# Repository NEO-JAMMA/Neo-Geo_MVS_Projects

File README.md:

THIS PROJECT IS PROVIDED "AS IS", WITHOUT WARRANTY OF ANY KIND, EXPRESS OR IMPLIED, INCLUDING BUT NOT LIMITED TO THE WARRANTIES OF MERCHANTABILITY, FITNESS FOR A PARTICULAR PURPOSE AND NONINFRINGEMENT. IN NO EVENT SHALL I BE LIABLE FOR ANY CLAIM, DAMAGES OR OTHER LIABILITY, WHETHER IN AN ACTION OF CONTRACT, TORT OR OTHERWISE, ARISING FROM, OUT OF OR IN CONNECTION WITH THIS PROJECT.

<b>Supergun for all MVS:</b><br>
https://github.com/NEO-JAMMA/Neo-Geo_MVS_Projects/tree/main/Supergun

<b>SNES to Neo-Geo Controller Adapter</b><br>
https://github.com/NEO-JAMMA/Neo-Geo_MVS_Projects/tree/main/ControllerAdapter

<b>RGB Csync to YPbPr NTSC Converter</b><br>
https://github.com/NEO-JAMMA/Neo-Geo_MVS_Projects/tree/main/RGBsToYPrBr

<b>Battery holder for MV1-C and MV1-B:</b><br>
https://github.com/NEO-JAMMA/Neo-Geo_MVS_Projects/blob/main/Battery

<b>Stereo mod is for MV1-B, MV1-A, and MV1FZ:</b><br>
https://github.com/NEO-JAMMA/Neo-Geo_MVS_Projects/blob/main/StereoMod

<b>ESP8266 Adapter for GBS8200</b><br>
https://github.com/NEO-JAMMA/Neo-Geo_MVS_Projects/blob/main/Esp8266ToGbs8200

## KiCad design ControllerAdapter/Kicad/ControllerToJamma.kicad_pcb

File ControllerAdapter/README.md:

THIS PROJECT IS PROVIDED "AS IS", WITHOUT WARRANTY OF ANY KIND, EXPRESS OR IMPLIED, INCLUDING BUT NOT LIMITED TO THE WARRANTIES OF MERCHANTABILITY, FITNESS FOR A PARTICULAR PURPOSE AND NONINFRINGEMENT. IN NO EVENT SHALL I BE LIABLE FOR ANY CLAIM, DAMAGES OR OTHER LIABILITY, WHETHER IN AN ACTION OF CONTRACT, TORT OR OTHERWISE, ARISING FROM, OUT OF OR IN CONNECTION WITH THIS PROJECT.

<b>SNES to Neo-Geo Controller Adapter</b>

<b>This converter is design to works with MVS supergun</b>
https://github.com/NEO-JAMMA/Neo-Geo_MVS_Projects/tree/main/Supergun/README.md

<b>Pictures of the all the Parts:</b><br>
https://github.com/NEO-JAMMA/Neo-Geo_MVS_Projects/tree/main/ControllerAdapter/Parts

<b>Parts description:</b>
- 1 * Arduino Nano (Cheap clone will works fine)
- 2 * Header 15 pins 2.54mm
- 1 * Micro Slide 90 Degree Switch 6 Pins DPDT PCB Mount
- 1 * Super Nintendo/Super Famicom controller port 90 Degree 7 Pin Female (if the controller port is reversed it is possible to reverse the pins by polling them and turning them to a 180 degree angle)
- 1 * DR15 15 Pins female right angle (D-SUB 15)
- 2 * Flat M3 Screws to replace the long hexagonal screw of DR15 15 Pins female port (to secure the front metal connector)

<b>Optional parts:</b>
- 4 * M2 Screws 25mm to 28mm long (For 3D printed case)

<b>Gerber files:</b><br>
https://github.com/NEO-JAMMA/Neo-Geo_MVS_Projects/tree/main/ControllerAdapter/Gerber

<b>Arduino code:</b><br>
https://github.com/NEO-JAMMA/Neo-Geo_MVS_Projects/tree/main/ControllerAdapter/ArduinoCode

<b>3D Printed case:</b><br>
https://github.com/NEO-JAMMA/Neo-Geo_MVS_Projects/tree/main/ControllerAdapter/3D_Case

<b>Kicad source:</b><br>
https://github.com/NEO-JAMMA/Neo-Geo_MVS_Projects/tree/main/ControllerAdapter/Kicad

<b>Controller Modes:</b><br>
The mode switch on the side of the PCB toggle the button mappings

<b>Other:</b>
- The controller adapter will have work with a Neo-Geo AES unfortunately the DB15 port is too short for Neo-Geo AES controller port.
- To program the Arduino Nano please refer to https://docs.arduino.cc/tutorials/nano/nano-getting-started/.
- The controller adapter works with Super Nintendo or Super Famicom controller (Cheap clones are fine).

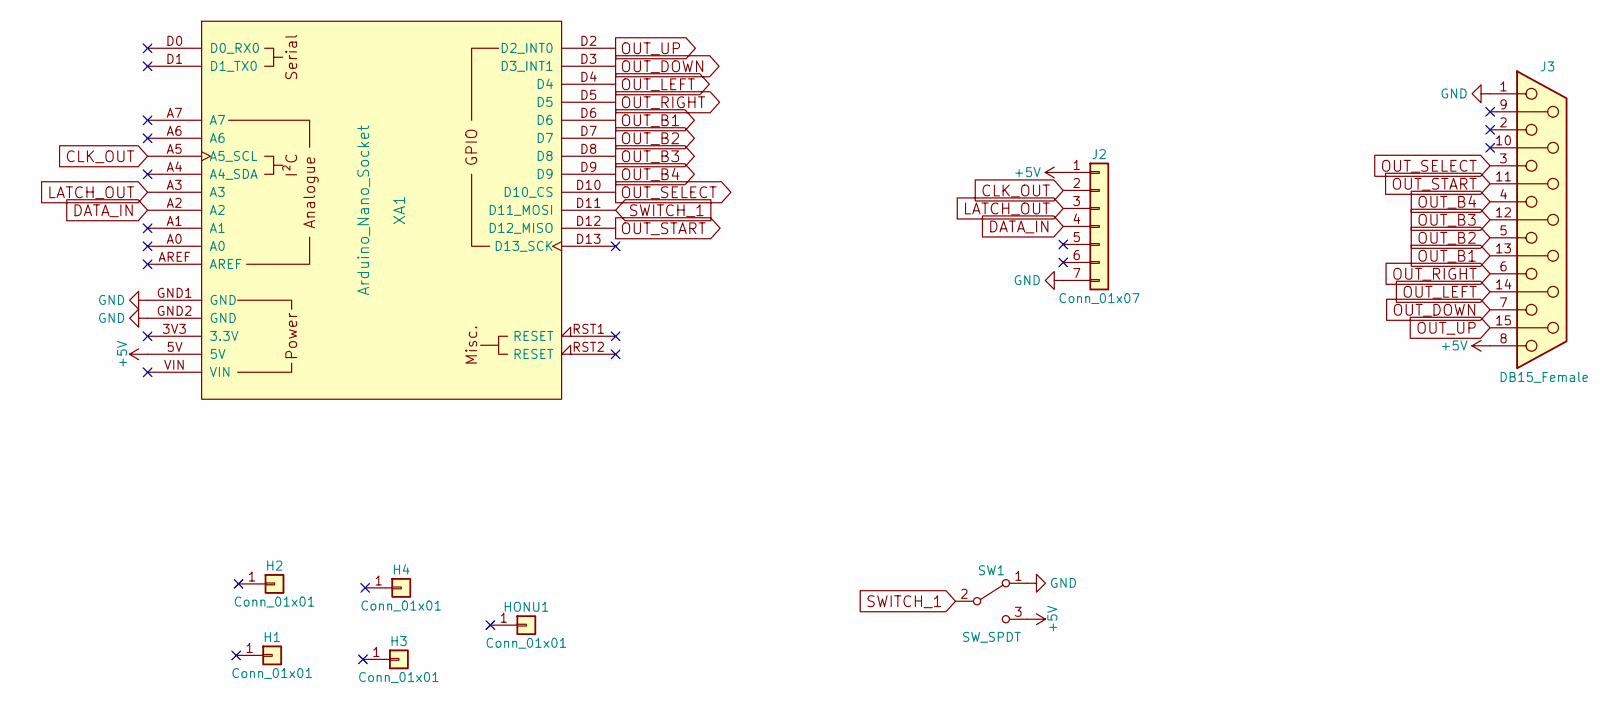
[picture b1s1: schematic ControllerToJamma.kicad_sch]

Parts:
H1, H2, H3, H4: Conn_01x01; MountingHole_2.5mm
HONU1: Conn_01x01; logo
J2: Conn_01x07; SNES_controller_port
J3: DB15_Female; DSUB-15_Female_Horizontal_Pitch2.77x2.84mm_EdgePinOffset4.9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
SW1: SW_SPDT; JS202011CQN
XA1: Arduino_Nano_Socket

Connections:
+5V: J2.1, J3.8, SW1.3 (C), XA1.5V
CLK_OUT: J2.2, XA1.A5 (A5_SCL)
DATA_IN: J2.4, XA1.A2
LATCH_OUT: J2.3, XA1.A3
OUT_B1: J3.13, XA1.D6
OUT_B2: J3.5, XA1.D7
OUT_B3: J3.12, XA1.D8
OUT_B4: J3.4, XA1.D9
OUT_DOWN: J3.7, XA1.D3 (D3_INT1)
OUT_LEFT: J3.14, XA1.D4
OUT_RIGHT: J3.6, XA1.D5
OUT_SELECT: J3.3, XA1.D10 (D10_CS)
OUT_START: J3.11 (P111), XA1.D12 (D12_MISO)
OUT_UP: J3.15, XA1.D2 (D2_INT0)
SWITCH_1: SW1.2 (B), XA1.D11 (D11_MOSI)
~: J2.7, J3.1, SW1.1 (A), XA1.GND1 (GND), XA1.GND2 (GND)

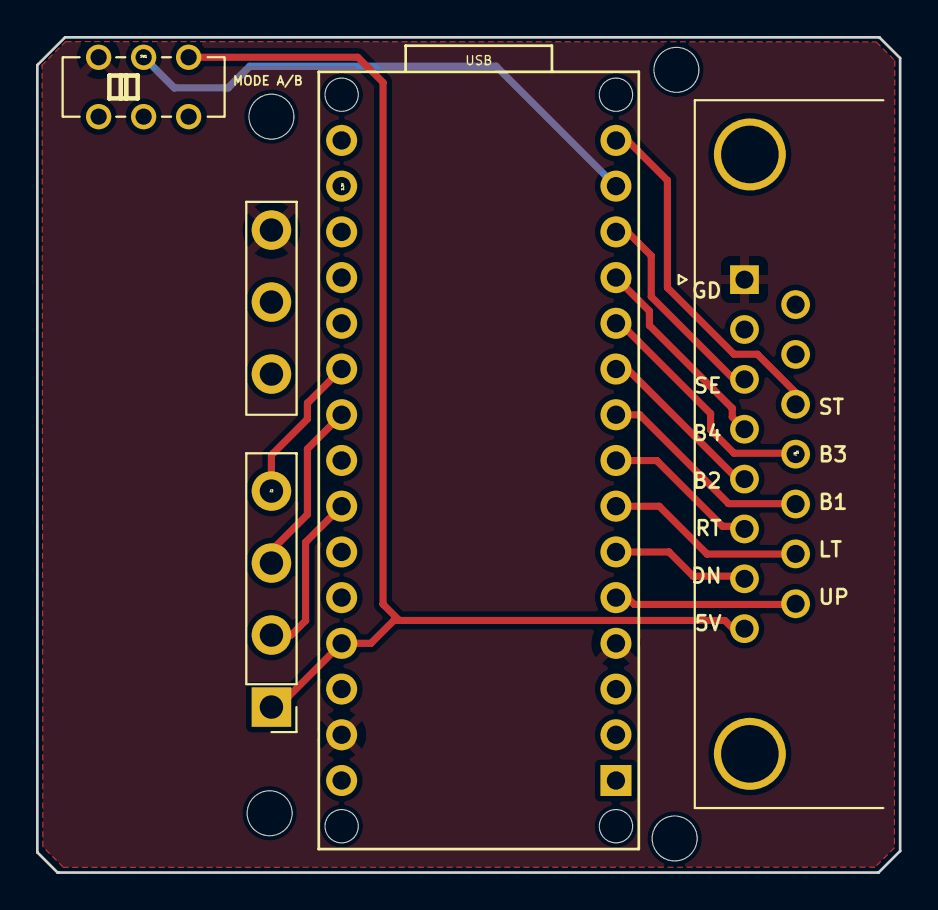
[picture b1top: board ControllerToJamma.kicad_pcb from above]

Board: 2 copper layers, 47.9 x 46.4 mm, 9 parts (1 on the bottom side), 16 nets.

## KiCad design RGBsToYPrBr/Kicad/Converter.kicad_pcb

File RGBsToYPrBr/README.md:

THIS PROJECT IS PROVIDED "AS IS", WITHOUT WARRANTY OF ANY KIND, EXPRESS OR IMPLIED, INCLUDING BUT NOT LIMITED TO THE WARRANTIES OF MERCHANTABILITY, FITNESS FOR A PARTICULAR PURPOSE AND NONINFRINGEMENT. IN NO EVENT SHALL I BE LIABLE FOR ANY CLAIM, DAMAGES OR OTHER LIABILITY, WHETHER IN AN ACTION OF CONTRACT, TORT OR OTHERWISE, ARISING FROM, OUT OF OR IN CONNECTION WITH THIS PROJECT.

<b>RGB Csync to YPbPr NTSC Converter</b>

<b>This Converter is design for this Supergun:</b><br>
https://github.com/NEO-JAMMA/Neo-Geo_MVS_Projects/tree/main/Supergun

<b>Pictures of the all the Parts:</b><br>

<b>Parts description:</b>
- 3 * 16V 220UF 6x7mm Electrolytic Capacitors
- 3 * 50V 1UF 4x7mm Electrolytic Capacitors
- 1 * 50V 10UF 4x7mm Electrolytic Capacitors
- 1 * 0.1UF Capacitors (104)
- 1 * 0.047UF Capacitors (473)
- 3 * 2sc945 transistors
- 1 * NTSC signal encoder BA7230LS
- 3 * PCB Mount RCA Female Connector
- 1 * 3F07 Audio Jack Connector PCB 5 Pins
- 1 * Header 8 Pins Male Socket Double Row 2.54mm (AV connection to the Supergun)
- 1 * 8 pins Dupont Cable Female Connector Wire 2.54mm Pitch 30cm (AV connection to the Supergun)
- 9 * Resistors
    - 6 * 75 Ohm
    - 2 * 20 Ohm
    - 1 * 62 Ohm

<b>Optional parts for powering the Supergun from the converter:</b>
- 3 * 18 gauge wires (12 Volt, 5 Volt, and ground connection to the Supergun)
- 1 * Molex 4 pins (PC connector)(12 Volt and 5 Volt connection to the Supergun)
- 1 * Power Jack Socket 2.1mm x 5.5mm Barrel-Type PCB Mount (5 Volt connection to the Supergun)

<b>Gerber files:</b><br>
https://github.com/NEO-JAMMA/Neo-Geo_MVS_Projects/tree/main/RGBsToYPrBr/Gerber

<b>Kicad source:</b><br>
https://github.com/NEO-JAMMA/Neo-Geo_MVS_Projects/tree/main/RGBsToYPrBr/Kicad

<b>Other:</b>
- The converter can also power the Supergun (see optional parts section)
- Acknowledgements to Ace, Zebidee and all variations available on the web which helped me for the design.
- Works only with NTSC TV not PAL/SECAM
- Only dislpay in 240p. For modern HDMI TV you need an upscaler like:
    - OSSC (https://www.retrorgb.com/ossc.html)
    - GBS8200 (https://github.com/ramapcsx2/gbs-control)

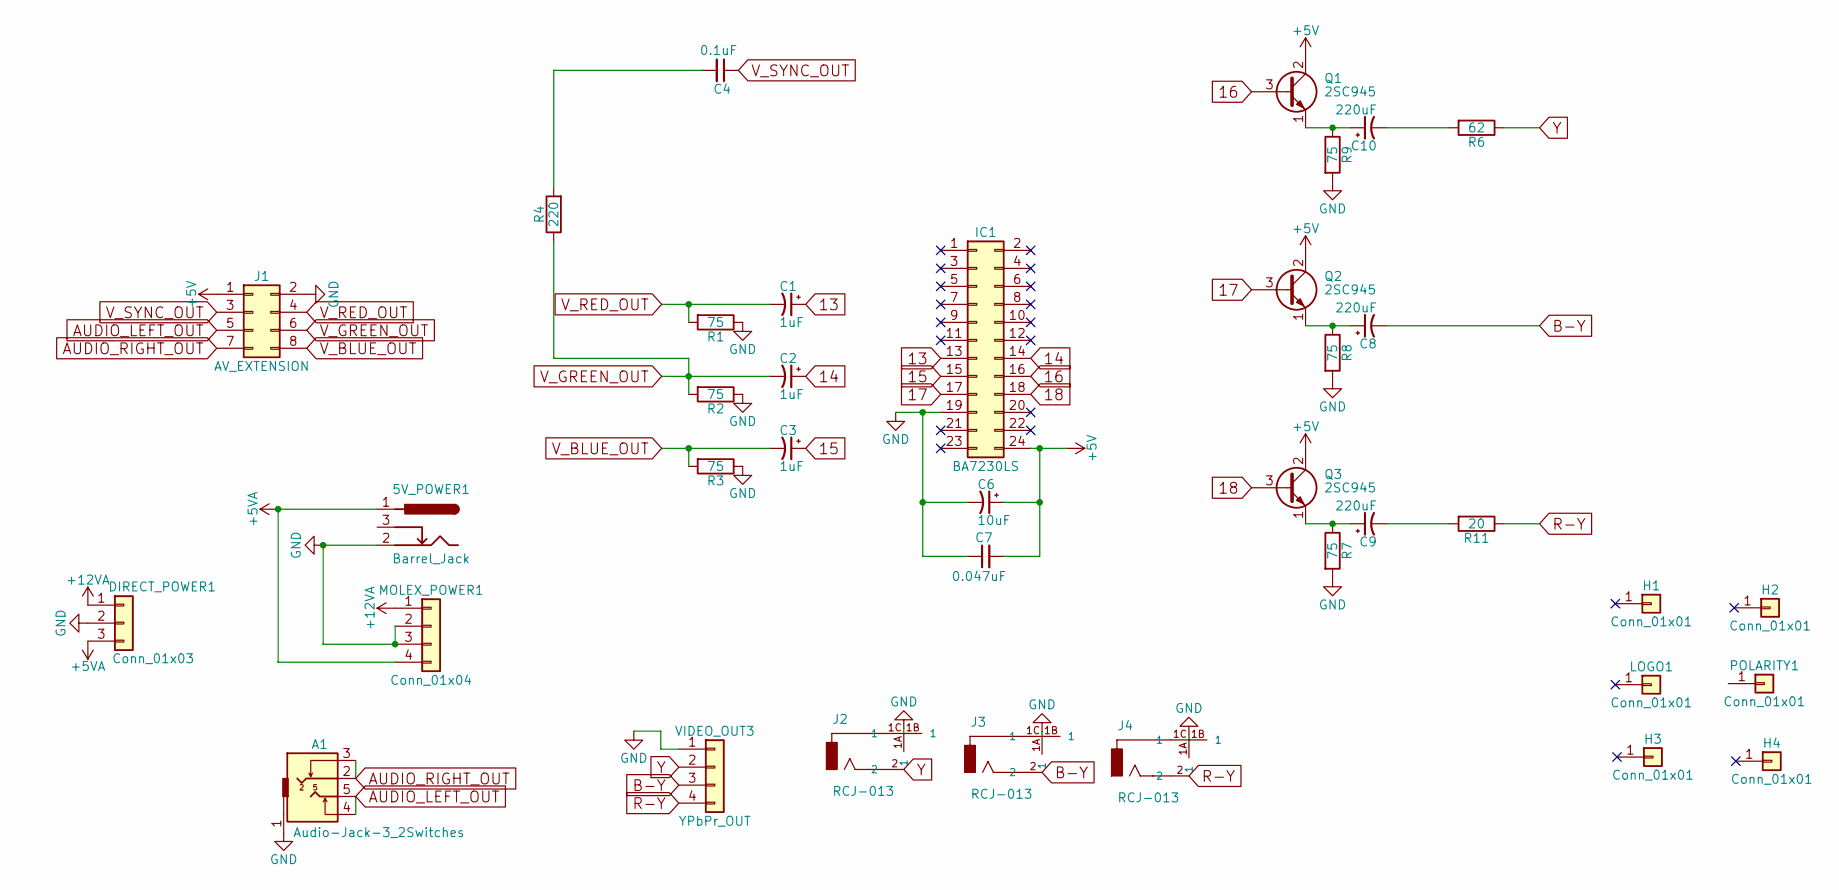
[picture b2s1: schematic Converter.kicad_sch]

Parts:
5V_POWER1: Barrel_Jack; BARREL_JACK
A1: Audio-Jack-3_2Switches; Tayda_3.5mm_stereo_TRS_jack_A-853
C1, C2, C3: 1uF; CP_Radial_D4.0mm_P1.50mm
C4: 0.1uF; C_Disc_D4.3mm_W1.9mm_P5.00mm
C6: 10uF; CP_Radial_D4.0mm_P1.50mm
C7: 0.047uF; C_Disc_D4.3mm_W1.9mm_P5.00mm
C8, C9, C10: 220uF; CP_Radial_D6.3mm_P2.50mm
DIRECT_POWER1: Conn_01x03; Power_03x2.54mm_Straight
H1, H2, H3, H4: Conn_01x01; 1pin
IC1: BA7230LS
J1: AV_EXTENSION; JTAG-8
J2, J3, J4: RCJ-013; CUI_RCJ-013
LOGO1: Conn_01x01; logo
MOLEX_POWER1: Conn_01x04; conn_hdd_15-24-4449
POLARITY1: Conn_01x01; Logo_silk_polarity_center_5x1.4mm
Q1, Q2, Q3: 2SC945; TO-92_Inline_Narrow_Oval
R1, R2, R3, R7, R8, R9: 75; R_Axial_DIN0204_L3.6mm_D1.6mm_P2.54mm_Vertical
R4: 220; R_Axial_DIN0204_L3.6mm_D1.6mm_P2.54mm_Vertical
R6: 62; R_Axial_DIN0204_L3.6mm_D1.6mm_P2.54mm_Vertical
R11: 20; R_Axial_DIN0204_L3.6mm_D1.6mm_P2.54mm_Vertical
VIDEO_OUT3: YPbPr_OUT; Pin_Header_Straight_1x04_Pitch2.54mm

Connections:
13: C1.1, IC1.13
14: C2.1, IC1.14
15: C3.1, IC1.15
16: IC1.16, Q1.3 (B)
17: IC1.17, Q2.3 (B)
18: IC1.18, Q3.3 (B)
+5V: C6.1, C7.2, IC1.24, J1.1, Q1.2 (C), Q2.2 (C), Q3.2 (C)
+5VA: 5V_POWER1.1, DIRECT_POWER1.3, MOLEX_POWER1.4
+12VA: DIRECT_POWER1.1, MOLEX_POWER1.1
AUDIO_LEFT_OUT: A1.4, A1.5, J1.5
AUDIO_RIGHT_OUT: A1.2, A1.3, J1.7
B-Y: C8.2, J3.2, VIDEO_OUT3.3
GND: 5V_POWER1.2, A1.1, C6.2, C7.1, DIRECT_POWER1.2, IC1.19, J1.2, J2.1A (1), J2.1B (1), J2.1C (1), J3.1A (1), J3.1B (1), J3.1C (1), J4.1A (1), J4.1B (1), J4.1C (1), MOLEX_POWER1.2, MOLEX_POWER1.3, R1.1, R2.1, R3.1, R7.2, R8.2, R9.2, VIDEO_OUT3.1
unnamed: C4.2, R4.2
unnamed: C8.1, Q2.1 (E), R8.1
unnamed: C9.1, Q3.1 (E), R7.1
unnamed: C9.2, R11.2
unnamed: C10.1, Q1.1 (E), R9.1
unnamed: C10.2, R6.2
R-Y: J4.2, R11.1, VIDEO_OUT3.4
V_BLUE_OUT: C3.2, J1.8, R3.2
V_GREEN_OUT: C2.2, J1.6, R2.2, R4.1
V_RED_OUT: C1.2, J1.4, R1.2
V_SYNC_OUT: C4.1, J1.3
Y: J2.2, R6.1, VIDEO_OUT3.2

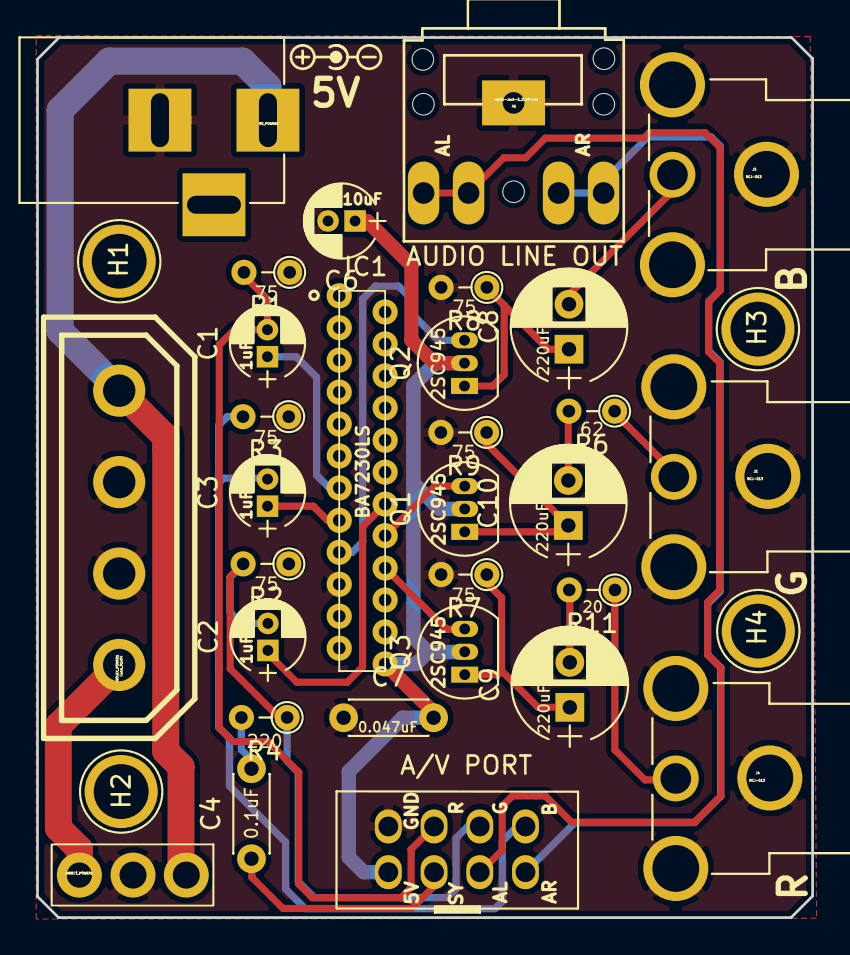
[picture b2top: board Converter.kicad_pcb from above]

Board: 2 copper layers, 43.1 x 48.9 mm, 36 parts (1 on the bottom side), 25 nets.

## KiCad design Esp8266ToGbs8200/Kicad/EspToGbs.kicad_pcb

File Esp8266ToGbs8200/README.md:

THIS PROJECT IS PROVIDED "AS IS", WITHOUT WARRANTY OF ANY KIND, EXPRESS OR IMPLIED, INCLUDING BUT NOT LIMITED TO THE WARRANTIES OF MERCHANTABILITY, FITNESS FOR A PARTICULAR PURPOSE AND NONINFRINGEMENT. IN NO EVENT SHALL I BE LIABLE FOR ANY CLAIM, DAMAGES OR OTHER LIABILITY, WHETHER IN AN ACTION OF CONTRACT, TORT OR OTHERWISE, ARISING FROM, OUT OF OR IN CONNECTION WITH THIS PROJECT.

<b>ESP8266 Adapter for GBS8200</b>

<b>This adapter is for mounting an ESP8266 to a GBS8200 with a custom Firmware:</b><br>
https://ramapcsx2.github.io/gbs-control<br>
https://github.com/ramapcsx2/gbs-control

<b>Pictures of the all the Parts:</b><br>

<b>Parts description:</b>
- 1 * PLCC44 socket
- 1 * Wemos D1 mini esp8266
- 2 * Header 8 pins 2.54mm

<b>Socket Preparation:</b><br>
The socket support must be cut to really fit tight to the IC

<b>Gerber files:</b><br>
https://github.com/NEO-JAMMA/Neo-Geo_MVS_Projects/tree/main/Esp8266ToGbs8200/Gerber

<b>3D Printed case:</b><br>
https://github.com/NEO-JAMMA/Neo-Geo_MVS_Projects/tree/main/Esp8266ToGbs8200/3D_Case

<b>Kicad source:</b><br>
https://github.com/NEO-JAMMA/Neo-Geo_MVS_Projects/tree/main/Esp8266ToGbs8200/Kicad

<b>Extensions:</b><br>
The PCB includes:
- A I2C header for the Si5351 Clock Generator https://ramapcsx2.github.io/gbs-control/Wiki/Si5351-Clock-Generator-install-notes.html
- A I2C header for the OLED Addon https://ramapcsx2.github.io/gbs-control/Wiki/OLED-Add-On-Setup-Info.html
- A IR header for a remote control (Not implemented yet)

<b>Programming of the Esp8266:</b><br>
https://ramapcsx2.github.io/gbs-control/Wiki/Software-Setup.html

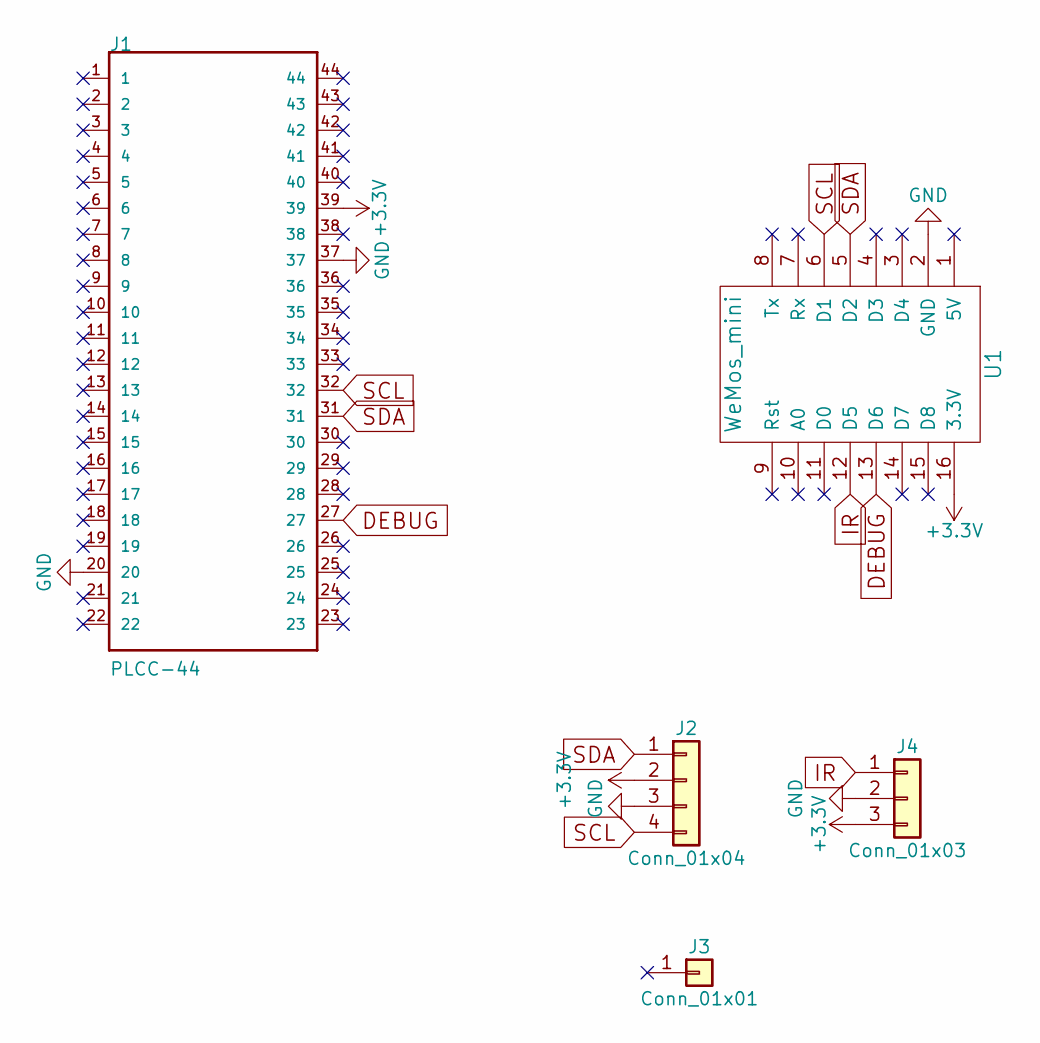
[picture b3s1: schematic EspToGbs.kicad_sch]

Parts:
J1: PLCC-44; PLCC-44_THT-Socket
J2: Conn_01x04; I2C
J3: Conn_01x01; logo
J4: Conn_01x03; IR
U1: WeMos_mini; D1_mini_board

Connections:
+3V3: J1.39, J2.2, J4.3, U1.16 (3.3V)
DEBUG: J1.27, U1.13 (D6)
GND: J1.20, J1.37, J2.3, J4.2, U1.2 (GND)
IR: J4.1, U1.12 (D5)
SCL: J1.32, J2.4, U1.6 (D1)
SDA: J1.31, J2.1, U1.5 (D2)

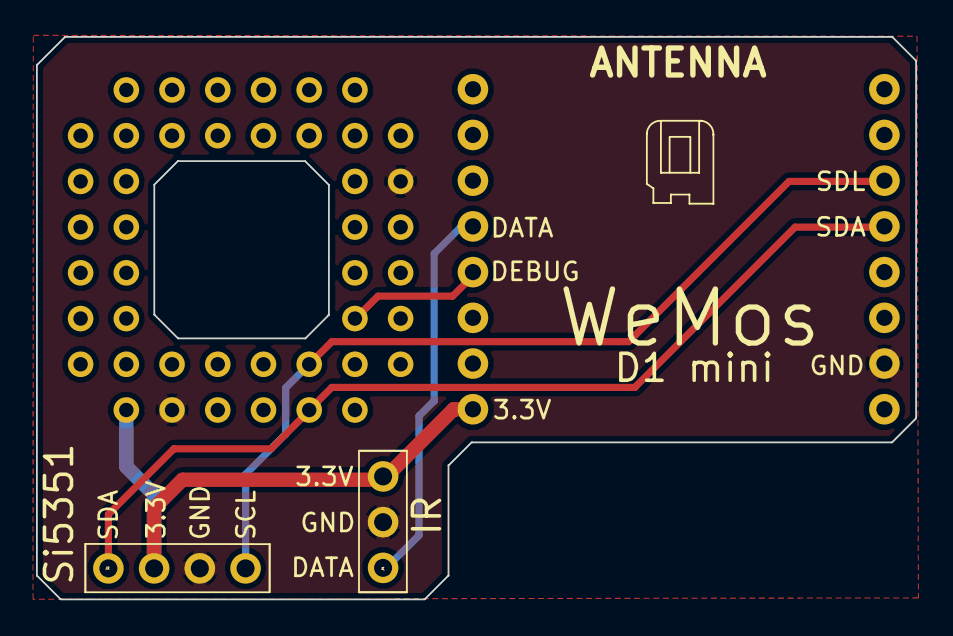
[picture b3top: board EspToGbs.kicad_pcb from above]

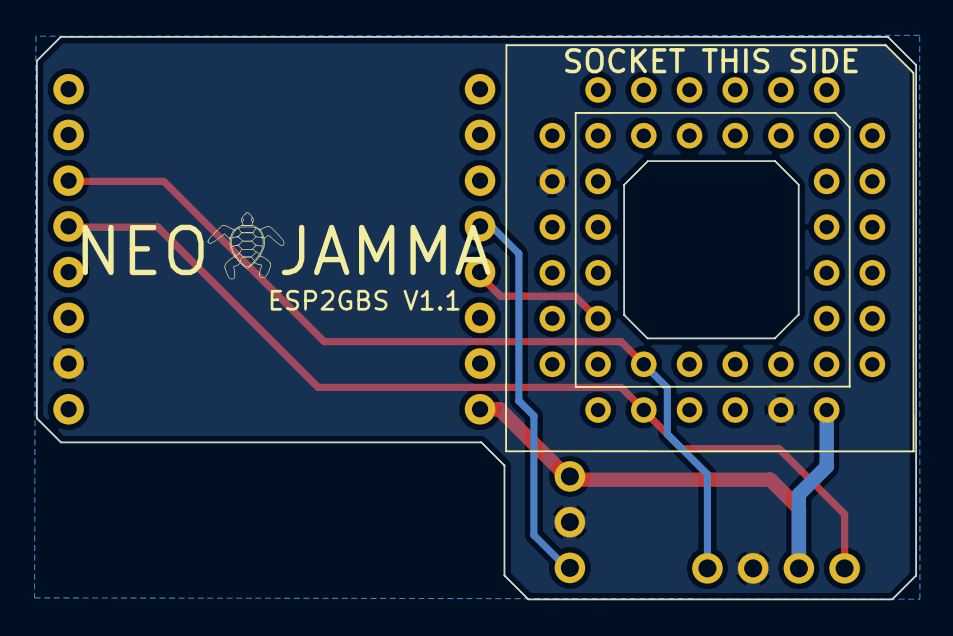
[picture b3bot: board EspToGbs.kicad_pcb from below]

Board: 2 copper layers, 48.8 x 31.3 mm, 5 parts (2 on the bottom side), 6 nets.

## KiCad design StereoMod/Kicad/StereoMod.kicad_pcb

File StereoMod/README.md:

THIS PROJECT IS PROVIDED "AS IS", WITHOUT WARRANTY OF ANY KIND, EXPRESS OR IMPLIED, INCLUDING BUT NOT LIMITED TO THE WARRANTIES OF MERCHANTABILITY, FITNESS FOR A PARTICULAR PURPOSE AND NONINFRINGEMENT. IN NO EVENT SHALL I BE LIABLE FOR ANY CLAIM, DAMAGES OR OTHER LIABILITY, WHETHER IN AN ACTION OF CONTRACT, TORT OR OTHERWISE, ARISING FROM, OUT OF OR IN CONNECTION WITH THIS PROJECT.

<b>This stereo mod is for :</b>
- MV1-B
- MV1-A
- MV1FZ

<b>Pictures of the all the Parts:</b><br>

<b>Parts description:</b>
- 4 * Resistors 1/4 watt 6.8K Ohm
- 4 * 50V 4.7UF 4x7mm Electrolytic Capacitors

<b>Gerber files:</b><br>
https://github.com/NEO-JAMMA/Neo-Geo_MVS_Projects/tree/main/StereoMod/Gerber

<b>Kicad source:</b><br>
https://github.com/NEO-JAMMA/Neo-Geo_MVS_Projects/tree/main/StereoMod/Kicad

<b>Wiring:</b><br>
Please check the Jamma Nation X tutorials for more information:
https://www.jamma-nation-x.com/jammax/tutorials.html

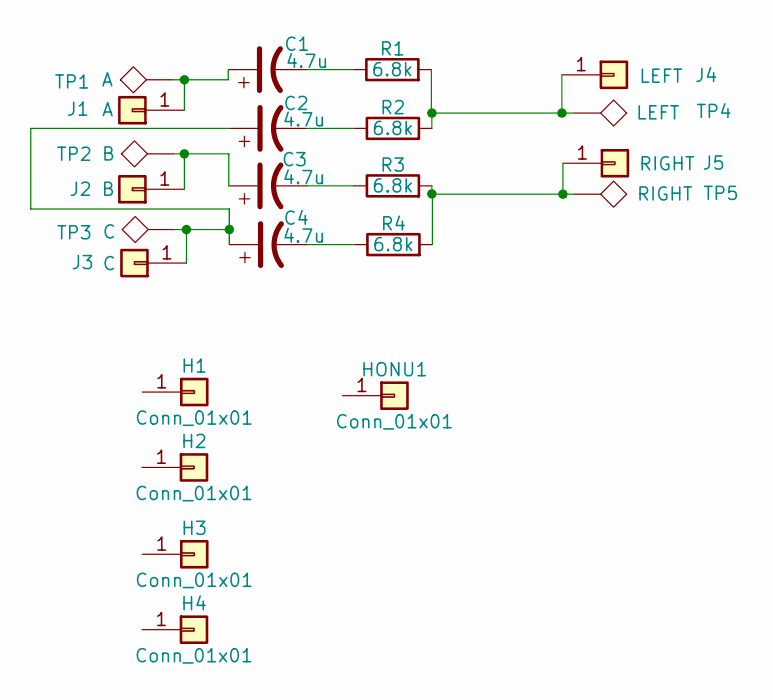
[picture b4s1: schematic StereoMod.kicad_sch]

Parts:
C1, C2, C3, C4: 4.7u; CP_Radial_D4.0mm_P2.00mm
H1, H2, H3, H4: Conn_01x01; 1pin
HONU1: Conn_01x01; logo
J1: A; Pin_Header_Straight_1x01_Pitch2.54mm
J2: B; Pin_Header_Straight_1x01_Pitch2.54mm
J3: C; Pin_Header_Straight_1x01_Pitch2.54mm
J4: LEFT; Pin_Header_Straight_1x01_Pitch2.54mm
J5: RIGHT; Pin_Header_Straight_1x01_Pitch2.54mm
R1, R2, R3, R4: 6.8k; R_Axial_DIN0207_L6.3mm_D2.5mm_P10.16mm_Horizontal
TP1: A; TestPoint_Pad_2.0x4.0mm
TP2: B; TestPoint_Pad_2.0x4.0mm
TP3: C; TestPoint_Pad_2.0x4.0mm
TP4: LEFT; TestPoint_Pad_2.0x4.0mm
TP5: RIGHT; TestPoint_Pad_2.0x4.0mm

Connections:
unnamed: C1.1, J1.1, TP1.1
unnamed: C1.2, R1.1
unnamed: C2.1, C4.1, J3.1, TP3.1
unnamed: C2.2, R2.1
unnamed: C3.1, J2.1, TP2.1
unnamed: C3.2, R3.1
unnamed: C4.2, R4.1
unnamed: J4.1, R1.2, R2.2, TP4.1
unnamed: J5.1, R3.2, R4.2, TP5.1

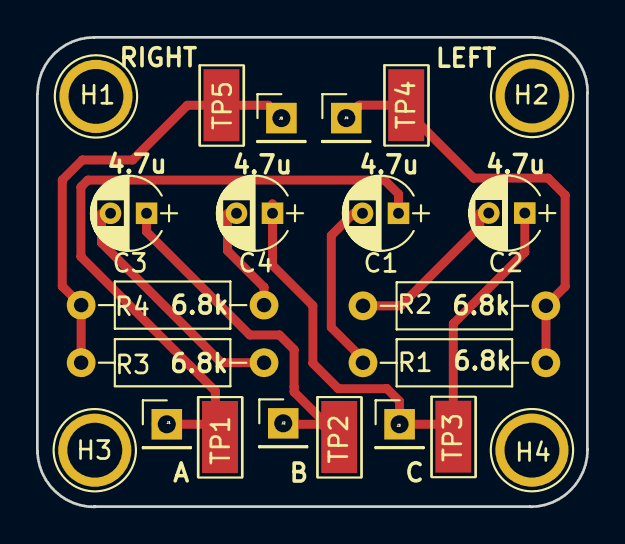
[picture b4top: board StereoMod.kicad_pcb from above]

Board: 2 copper layers, 30.6 x 26.1 mm, 23 parts (1 on the bottom side), 9 nets.

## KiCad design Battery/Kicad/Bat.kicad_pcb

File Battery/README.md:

THIS PROJECT IS PROVIDED "AS IS", WITHOUT WARRANTY OF ANY KIND, EXPRESS OR IMPLIED, INCLUDING BUT NOT LIMITED TO THE WARRANTIES OF MERCHANTABILITY, FITNESS FOR A PARTICULAR PURPOSE AND NONINFRINGEMENT. IN NO EVENT SHALL I BE LIABLE FOR ANY CLAIM, DAMAGES OR OTHER LIABILITY, WHETHER IN AN ACTION OF CONTRACT, TORT OR OTHERWISE, ARISING FROM, OUT OF OR IN CONNECTION WITH THIS PROJECT.

<b>This battery holder is for replacing the battery coin of the MVS:</b>
- MV1-C (the battery holder can be mounted vertically only)
- MV1-B (the battery holder can be mounted vertically or horizontally)

<b>Pictures of the all the Parts:</b><br>
https://github.com/NEO-JAMMA/Neo-Geo_MVS_Projects/tree/main/Battery/Parts

<b>Parts description:</b>
- 1 * SMD Button Coin Cell CR2032 battery holder
- 3 * Header 1 pin 2.54mm 90 degree right angle (for vertical mount)
- or
- 3 * Header 1 pin 2.54mm (for horizontal mount)

<b>Optional parts:</b>
- 1 * LIR2032 3.6V Li-ion rechargeable battery
- or
- 1 * CR2032 3V none rechargeable battery

<b>Soldering of the header pins for vertical mount:</b>

<b>Gerber files:</b><br>
https://github.com/NEO-JAMMA/Neo-Geo_MVS_Projects/tree/main/Battery/Gerber

<b>Kicad source:</b><br>
https://github.com/NEO-JAMMA/Neo-Geo_MVS_Projects/tree/main/Battery/Kicad

<b>CR2032 vs LIR2032</b><br>
if you want to use a CR2032 none rechargeable battery it is important to remove some components please check the Jamma Nation X tutorials for more information:
https://www.jamma-nation-x.com/jammax/tutorials.html

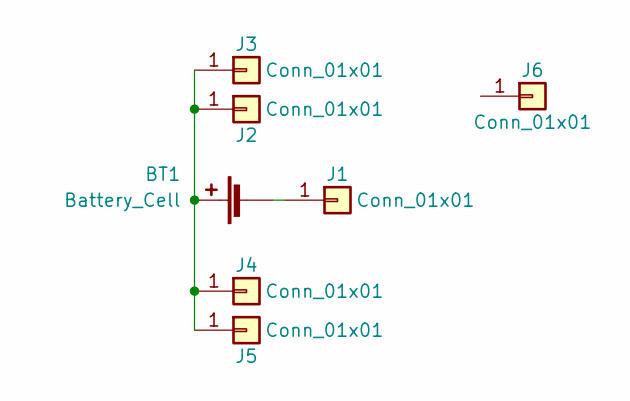
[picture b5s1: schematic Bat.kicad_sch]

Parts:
BT1: Battery_Cell; Keystone_3034_1x20mm-CoinCell
J1, J2, J3, J4, J5: Conn_01x01; Pin_Header_Straight_1x01_Pitch2.54mm
J6: Conn_01x01; logo

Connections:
unnamed: BT1.1 (+), J2.1, J3.1, J4.1, J5.1
unnamed 1: BT1.2 (-), J1.1; also elsewhere on the board

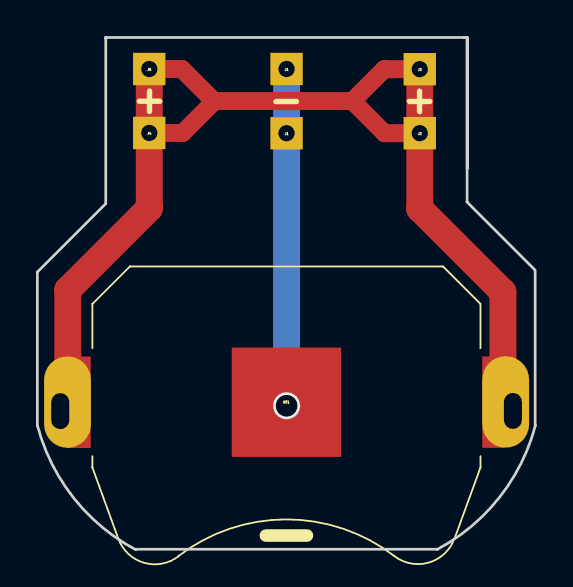
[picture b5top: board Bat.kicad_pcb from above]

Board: 2 copper layers, 27.7 x 28.5 mm, 8 parts (1 on the bottom side), 2 nets.

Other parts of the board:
J1#2: Conn_01x01; Pin_Header_Straight_1x01_Pitch2.54mm

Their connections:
unnamed 1: J1#2.1; also elsewhere on the board

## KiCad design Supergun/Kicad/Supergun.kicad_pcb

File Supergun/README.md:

THIS PROJECT IS PROVIDED "AS IS", WITHOUT WARRANTY OF ANY KIND, EXPRESS OR IMPLIED, INCLUDING BUT NOT LIMITED TO THE WARRANTIES OF MERCHANTABILITY, FITNESS FOR A PARTICULAR PURPOSE AND NONINFRINGEMENT. IN NO EVENT SHALL I BE LIABLE FOR ANY CLAIM, DAMAGES OR OTHER LIABILITY, WHETHER IN AN ACTION OF CONTRACT, TORT OR OTHERWISE, ARISING FROM, OUT OF OR IN CONNECTION WITH THIS PROJECT.

<b>Universal MVS Supergun</b>

<b>This supergun works with all MVS and Atomiswave (use the Kick Harness pins for Atomiswave)</b>

<b>Pictures of the all the Parts:</b><br>
https://github.com/NEO-JAMMA/Neo-Geo_MVS_Projects/tree/main/Supergun/Parts

<b>Parts description:</b>
- 1 * 28 pins JAMMA Connector
- 3 * RM065 500 Ohm Potentiometer
- 3 * Button 6mm x 6mm x 12.5mm
- 4 * 16V 220UF 6x7mm Electrolytic Capacitors
- 1 * KCD2-202 DPDT Switch 6 pins 21X15mm
- 1 * Mini Din9 9 Pins Connector
- 1 * Molex 4 pins (PC connector) (Optional With Direct Stereo Audio/5 volts mod)
- 1 * Power Jack Socket 2.1mm x 5.5mm Barrel-Type PCB Mount
- 2 * Header 3 pins 2.54mm
- 2 * DR15 15 Pins Male right angle (D-SUB 15)
- 1 * 3F07 Audio Jack Connector PCB 5 Pins
- 2 * Led 3mm (Orange & Red)
- 7 * Resistors
    - 1 * 470 Ohm
    - 1 * 330 Ohm
    - 1 * 680 Ohm
    - 2 * 1K Ohm (Optional With Direct Stereo Audio/5 volts mod)
    - 2 * 10K Ohm (Optional With Direct Stereo Audio/5 volts mod)

<b>Optional parts:</b>
- 1 * 2 pins Dupont Cable Female Connector Wire 2.54mm Pitch 30cm (For Stereo audio connection directly to the MVS)
- 1 * Header 3 pins 2.54mm (For Kick Harness)
- 1 * KF301-2P 5.08mm 2 Pins Connect Terminal Screw (External 5 Volts/12 Volts)
- 1 * Header 8 Pins Male Socket Double Row Right Angle 2.54mm (External A/V signal)
- 5 * M3 Screws 5mm long (For 3D printed case)

<b>Soldering of the JAMMA header:</b>

<b>Gerber files:</b><br>
https://github.com/NEO-JAMMA/Neo-Geo_MVS_Projects/tree/main/Supergun/Gerber

<b>3D Printed case:</b><br>
https://github.com/NEO-JAMMA/Neo-Geo_MVS_Projects/tree/main/Supergun/3D_Case

<b>Kicad source:</b><br>
https://github.com/NEO-JAMMA/Neo-Geo_MVS_Projects/tree/main/Supergun/Kicad

<b>Inputs Voltage:</b><br>
- The recommended power supply sould be at least 3 amp.
- The supergun can be power by the 5 Volts Barrel power jack (2.1mm x 5.5mm)(Center positive) or by the 5 volts/12 volts Molex connector depending on the sound configuration. Please see below.

<b>For the sound:</b>
- If you have the direct stereo modification on your MVS just put the two sound wires from the MVS (left-right) on the "DIRECT" connector, no jumper on "LEFT" and "RIGHT" connector. You can power the board by the Barrel power jack only 5 volts are needed.

- if you don't have the direct stereo modification (sound comming form the JAMMA connector) you need to use the two jumpers on "LEFT" and "RIGHT" connector and you need to use the Molex connector 5 volts/12 volts.

<b>For the video:</b>
- This Supergun only dislpay in 240p. For HDMI TV you need an upscaler like:
    - OSSC (https://www.retrorgb.com/ossc.html)
    - GBS8200 (https://github.com/NEO-JAMMA/Neo-Geo_MVS_Projects/tree/main/Esp8266ToGbs8200)
- The video signal is safe thanks to the 470 Ohm on the video Sync signal.
- For best image/sound quality use a shielded cable.
- The 3 blue potentiometers allow a fine tunning of the RGB colors.
- This Supergun is designed to be used with a Genesis/Megadrive 2 AV cable: 

<b>Other:</b>
- Depending on your setup you might have to cut the test jumper on the bottom PCB. Usually one slot MVS use the JAMMA test pin (default) - Multi-slot use the MVS.
- CP1 & CP2 are the coin buttons for player 1 & 2
- On the right to JAMMA connector a 3 pins header (5 volts, ground, and 12 volts) is for external power.
- Near the sound pins is located an extenal 8 pins A/V header for additional A/V outputs.
- For stereo mod please check the Jamma Nation X tutorials for more information:
https://www.jamma-nation-x.com/jammax/tutorials.html

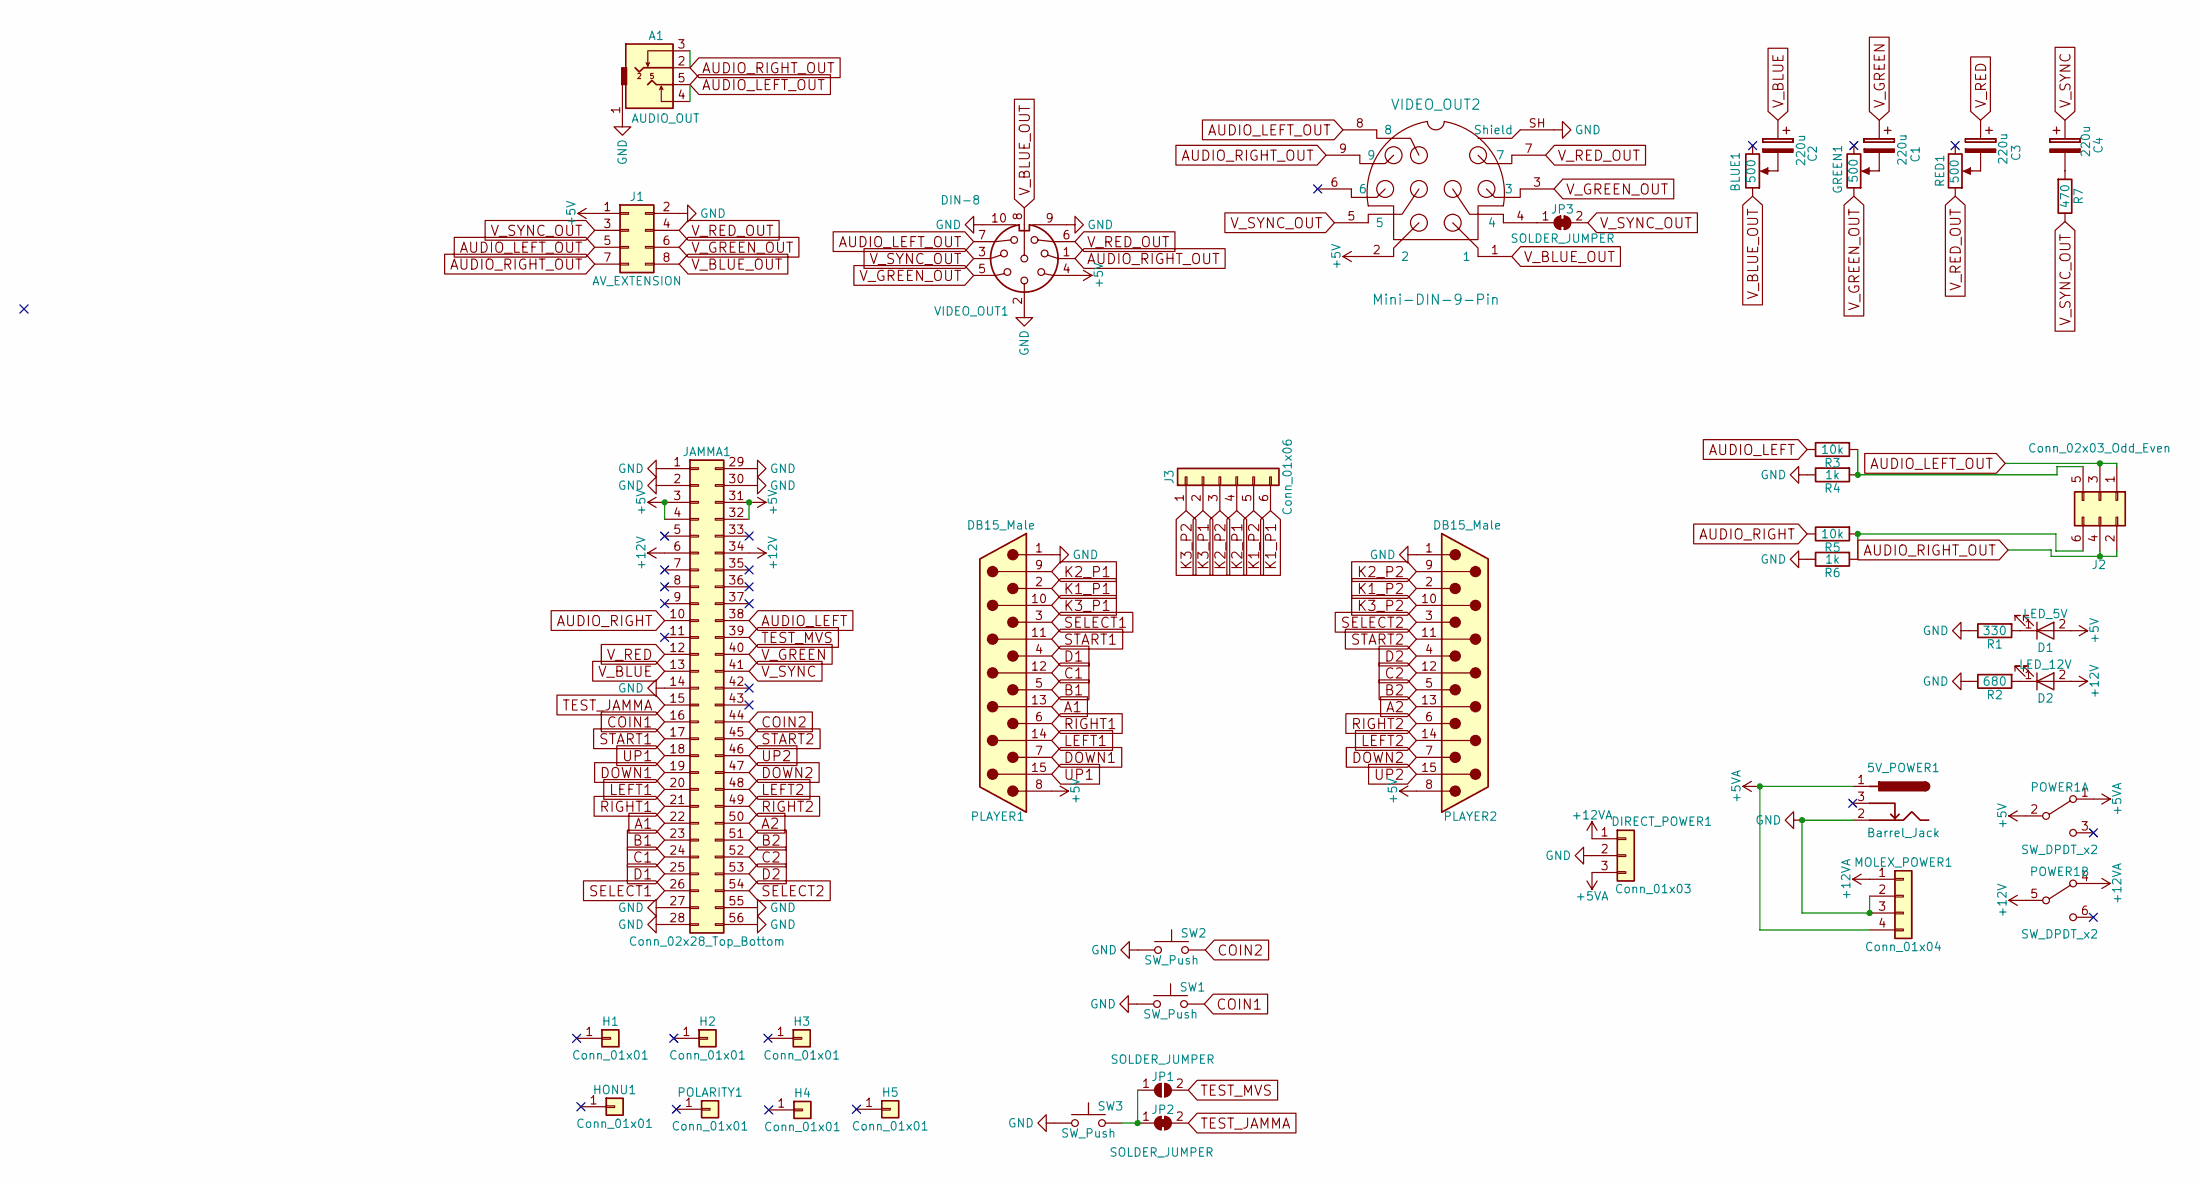
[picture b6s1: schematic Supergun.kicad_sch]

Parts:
5V_POWER1: Barrel_Jack; BARREL_JACK
A1: AUDIO_OUT; Tayda_3.5mm_stereo_TRS_jack_A-853
BLUE1: 500; Potentiometer
C1, C2, C3, C4: 220u; CP_Radial_D6.3mm_P2.50mm
D1: LED_5V; LED_D3.0mm
D2: LED_12V; LED_D3.0mm
DIRECT_POWER1: Conn_01x03; Power_03x2.54mm_Straight
GREEN1: 500; Potentiometer
H1, H2, H3, H4, H5: Conn_01x01; 1pin
HONU1: Conn_01x01; logo
J1: AV_EXTENSION; JTAG-8
J2: Conn_02x03_Odd_Even; Pin_Header_Straight_2x03_Pitch2.54mm
J3: Conn_01x06; kick_harness
JAMMA1: Conn_02x28_Top_Bottom; Jamma_28f
JP1: SOLDER_JUMPER; SolderJumper-2_P1.3mm_Open_Pad1.0x1.5mm
JP2, JP3: SOLDER_JUMPER; SolderJumper-2_P1.3mm_Bridged_Pad1.0x1.5mm
MOLEX_POWER1: Conn_01x04; conn_hdd_15-24-4449
PLAYER1, PLAYER2: DB15_Male; DSUB-15_Male_Horizontal_Pitch2.77x2.84mm_EdgePinOffset4.94m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
POLARITY1: Conn_01x01; Logo_silk_polarity_center_5x1.4mm
POWER1: SW_DPDT_x2; KCD1-101
R1: 330; R_Axial_DIN0207_L6.3mm_D2.5mm_P10.16mm_Horizontal
R2: 680; R_Axial_DIN0207_L6.3mm_D2.5mm_P10.16mm_Horizontal
R3, R5: 10k; R_Axial_DIN0207_L6.3mm_D2.5mm_P10.16mm_Horizontal
R4, R6: 1k; R_Axial_DIN0207_L6.3mm_D2.5mm_P10.16mm_Horizontal
R7: 470; R_Axial_DIN0207_L6.3mm_D2.5mm_P10.16mm_Horizontal
RED1: 500; Potentiometer
SW1, SW2, SW3: SW_Push; SW_PUSH_6mm
VIDEO_OUT1: DIN-8; din-8
VIDEO_OUT2: Mini-DIN-9-Pin; MINI-DIN-9PIN

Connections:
+5V: D1.2 (A), J1.1, JAMMA1.3, JAMMA1.4, JAMMA1.31, JAMMA1.32, PLAYER1.8, PLAYER2.8, POWER1.2 (B), VIDEO_OUT1.4, VIDEO_OUT2.2
+5VA: 5V_POWER1.1, DIRECT_POWER1.3, MOLEX_POWER1.4, POWER1.1 (A)
+12V: D2.2 (A), JAMMA1.6, JAMMA1.34, POWER1.5 (B)
+12VA: DIRECT_POWER1.1, MOLEX_POWER1.1, POWER1.4 (A)
A1: JAMMA1.22, PLAYER1.13
A2: JAMMA1.50, PLAYER2.13
AUDIO_LEFT: JAMMA1.38, R3.1
AUDIO_LEFT_OUT: A1.4, A1.5, J1.5, J2.1, J2.3, VIDEO_OUT1.7, VIDEO_OUT2.8
AUDIO_RIGHT: JAMMA1.10, R5.1
AUDIO_RIGHT_OUT: A1.2, A1.3, J1.7, J2.2, J2.4, VIDEO_OUT1.1, VIDEO_OUT2.9
B1: JAMMA1.23, PLAYER1.5
B2: JAMMA1.51, PLAYER2.5
C1: JAMMA1.24, PLAYER1.12
C2: JAMMA1.52, PLAYER2.12
COIN1: JAMMA1.16, SW1.2
COIN2: JAMMA1.44, SW2.2
D1: JAMMA1.25, PLAYER1.4
D2: JAMMA1.53, PLAYER2.4
DOWN1: JAMMA1.19, PLAYER1.7
DOWN2: JAMMA1.47, PLAYER2.7
K1_P1: J3.6, PLAYER1.2
K1_P2: J3.5, PLAYER2.2
K2_P1: J3.4, PLAYER1.9
K2_P2: J3.3, PLAYER2.9
K3_P1: J3.2, PLAYER1.10
K3_P2: J3.1, PLAYER2.10
LEFT1: JAMMA1.20, PLAYER1.14
LEFT2: JAMMA1.48, PLAYER2.14
unnamed: BLUE1.2, C2.2
unnamed: C1.2, GREEN1.2
unnamed: C3.2, RED1.2
unnamed: C4.2, R7.2
unnamed: D1.1 (K), R1.2
unnamed: D2.1 (K), R2.2
unnamed: J2.5, R3.2, R4.2
unnamed: J2.6, R5.2, R6.2
unnamed: JP1.1 (A), JP2.1 (A), SW3.2
unnamed: JP3.1 (A), VIDEO_OUT2.4
RIGHT1: JAMMA1.21, PLAYER1.6
RIGHT2: JAMMA1.49, PLAYER2.6
SELECT1: JAMMA1.26, PLAYER1.3
SELECT2: JAMMA1.54, PLAYER2.3
START1: JAMMA1.17, PLAYER1.11 (P111)
START2: JAMMA1.45, PLAYER2.11 (P111)
TEST_JAMMA: JAMMA1.15, JP2.2 (B)
TEST_MVS: JAMMA1.39, JP1.2 (B)
UP1: JAMMA1.18, PLAYER1.15
UP2: JAMMA1.46, PLAYER2.15
V_BLUE: C2.1, JAMMA1.13
V_BLUE_OUT: BLUE1.1, J1.8, VIDEO_OUT1.8, VIDEO_OUT2.1
V_GREEN: C1.1, JAMMA1.40
V_GREEN_OUT: GREEN1.1, J1.6, VIDEO_OUT1.5, VIDEO_OUT2.3
V_RED: C3.1, JAMMA1.12
V_RED_OUT: J1.4, RED1.1, VIDEO_OUT1.6, VIDEO_OUT2.7
V_SYNC: C4.1, JAMMA1.41
V_SYNC_OUT: J1.3, JP3.2 (B), R7.1, VIDEO_OUT1.3, VIDEO_OUT2.5
~: 5V_POWER1.2, A1.1, DIRECT_POWER1.2, J1.2, JAMMA1.1, JAMMA1.2, JAMMA1.14, JAMMA1.27, JAMMA1.28, JAMMA1.29, JAMMA1.30, JAMMA1.55, JAMMA1.56, MOLEX_POWER1.2, MOLEX_POWER1.3, PLAYER1.1, PLAYER2.1, R1.1, R2.1, R4.1, R6.1, SW1.1, SW2.1, SW3.1, VIDEO_OUT1.2, VIDEO_OUT1.9, VIDEO_OUT1.10, VIDEO_OUT2.SH (Shield)

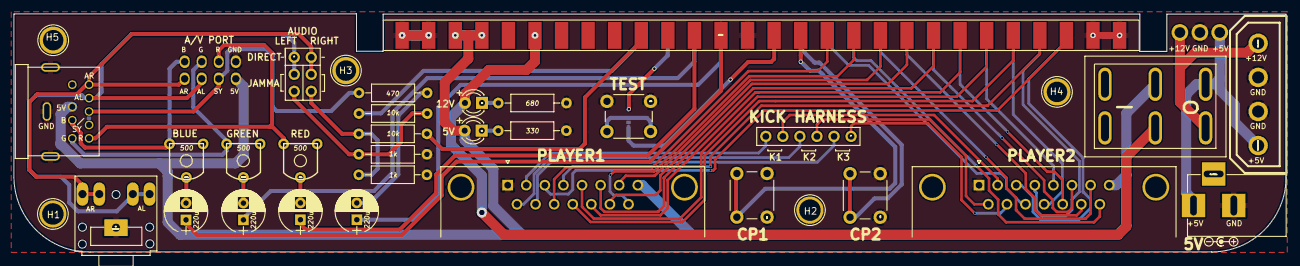
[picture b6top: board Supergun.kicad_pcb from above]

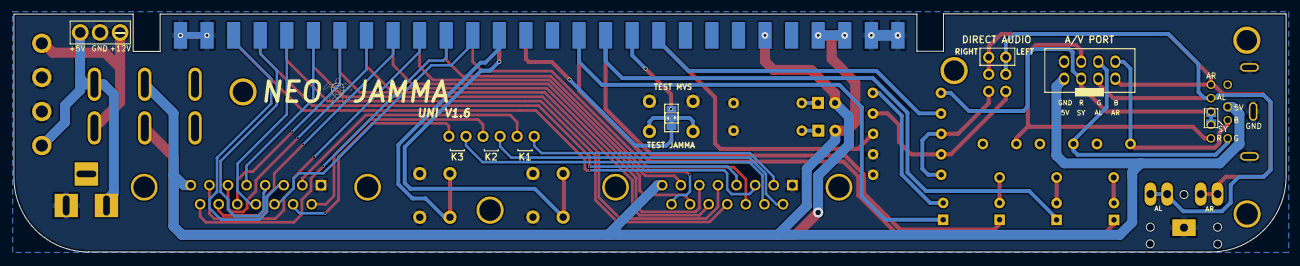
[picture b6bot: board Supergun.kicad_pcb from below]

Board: 2 copper layers, 189.6 x 35.5 mm, 41 parts (6 on the bottom side), 57 nets.

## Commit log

2025-03-02 Supergun commit
2025-03-07 Add Battery Holder
2025-03-07 Remove extra pics
2025-03-07 Add StereoMod
2025-03-15 Add Esp8266ToGbs8200
2025-03-16 Add RGBsToYPrBr
2025-03-16 Update images
2025-04-19 Remove Backup
2025-04-20 Fix DR15
2025-04-20 Add Header
2025-04-20 Add ControllerAdapter
